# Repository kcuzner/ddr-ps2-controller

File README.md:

# Dance-Dance-Revolution PS2 Controller

Kevin Cuzner

## Introduction

This is my attempt at a low-cost, but high quality DIY DDR controller which is compatible with the Sony PlayStation 2.

The firmware is based loosely on my [Pop-N-Music PS2 Controller](https://github.com/kcuzner/pop-n-music-controller).
though I've rewritten it to be closer to my current style.

Although it would be cool to use an STM32 or other advanced ARM controller, that is overkill for what this is. Turns
out, a $0.60 AVR microcontroller can meet all the digital requirements without even needing a 3.3V regulator. To that
end, here is the main featureset:

 - ATTiny20 microcontroller (QFN package, 12 I/O). There are two personalities:
   - The PSX bus interface. This takes input from up to 6 buttons and operates the upstream PSX bus to the PlayStation
     2.
   - The switch controller. This takes input from up to 4 foot switches and produces a single output which is cabled to
     the PSX bux interface board.
 - Single PCB which fits both personalities.
 - Edge-facing LEDs for pad illumination.
   - Strangely enough, it was cheaper to just use a constant-current controlled LED driver than to use a discrete MOSFET
     of an appropriate size.

## Project Status

 - This project has not been fully assembled or tested. But:
 - Firmware builds and installs on both board personalities.
 - The LED/Switch boards work great! Mostly. Some quirks with the LEDs always being partially on,
   but whatever.
 - With a [USB-PS2 adapter](https://www.amazon.com/gp/product/B01J4JVFXI) I've verified on an
   oscilloscope that the controller board can be polled and that it appears to send back the
   correct responses. So the PSX bus implementation is at least superficially correct.
 - The switch boards can connect to the controller board and on an oscilloscope I've verified that
   everything toggles.

Some things still remain I can think of off the top of my head:

 - I need to test it with an actual PS2. Now to convince my wife to let me touch her PS2...
 - I need to verify that the button/switch mappings are correct for a dance pad. I unfortunately
   didn't mark the PCB silkscreen in any way for that, so I'm going to have to resort to colored
   tape, paint, or something else to keep the myriad cables straight while wiring this up.
 - I need to actually construct the wood/metal/plastic enclosure for this. I have a plan, but it's
   not posted here.

## References

 - http://www.raphnet.net/electronique/psx_adaptor/Playstation.txt
 - https://gist.github.com/scanlime/5042071
 - https://store.curiousinventor.com/guides/PS2/
 - https://blog.nearfuturelaboratory.com/2008/06/19/playstation2-logic-analysis/

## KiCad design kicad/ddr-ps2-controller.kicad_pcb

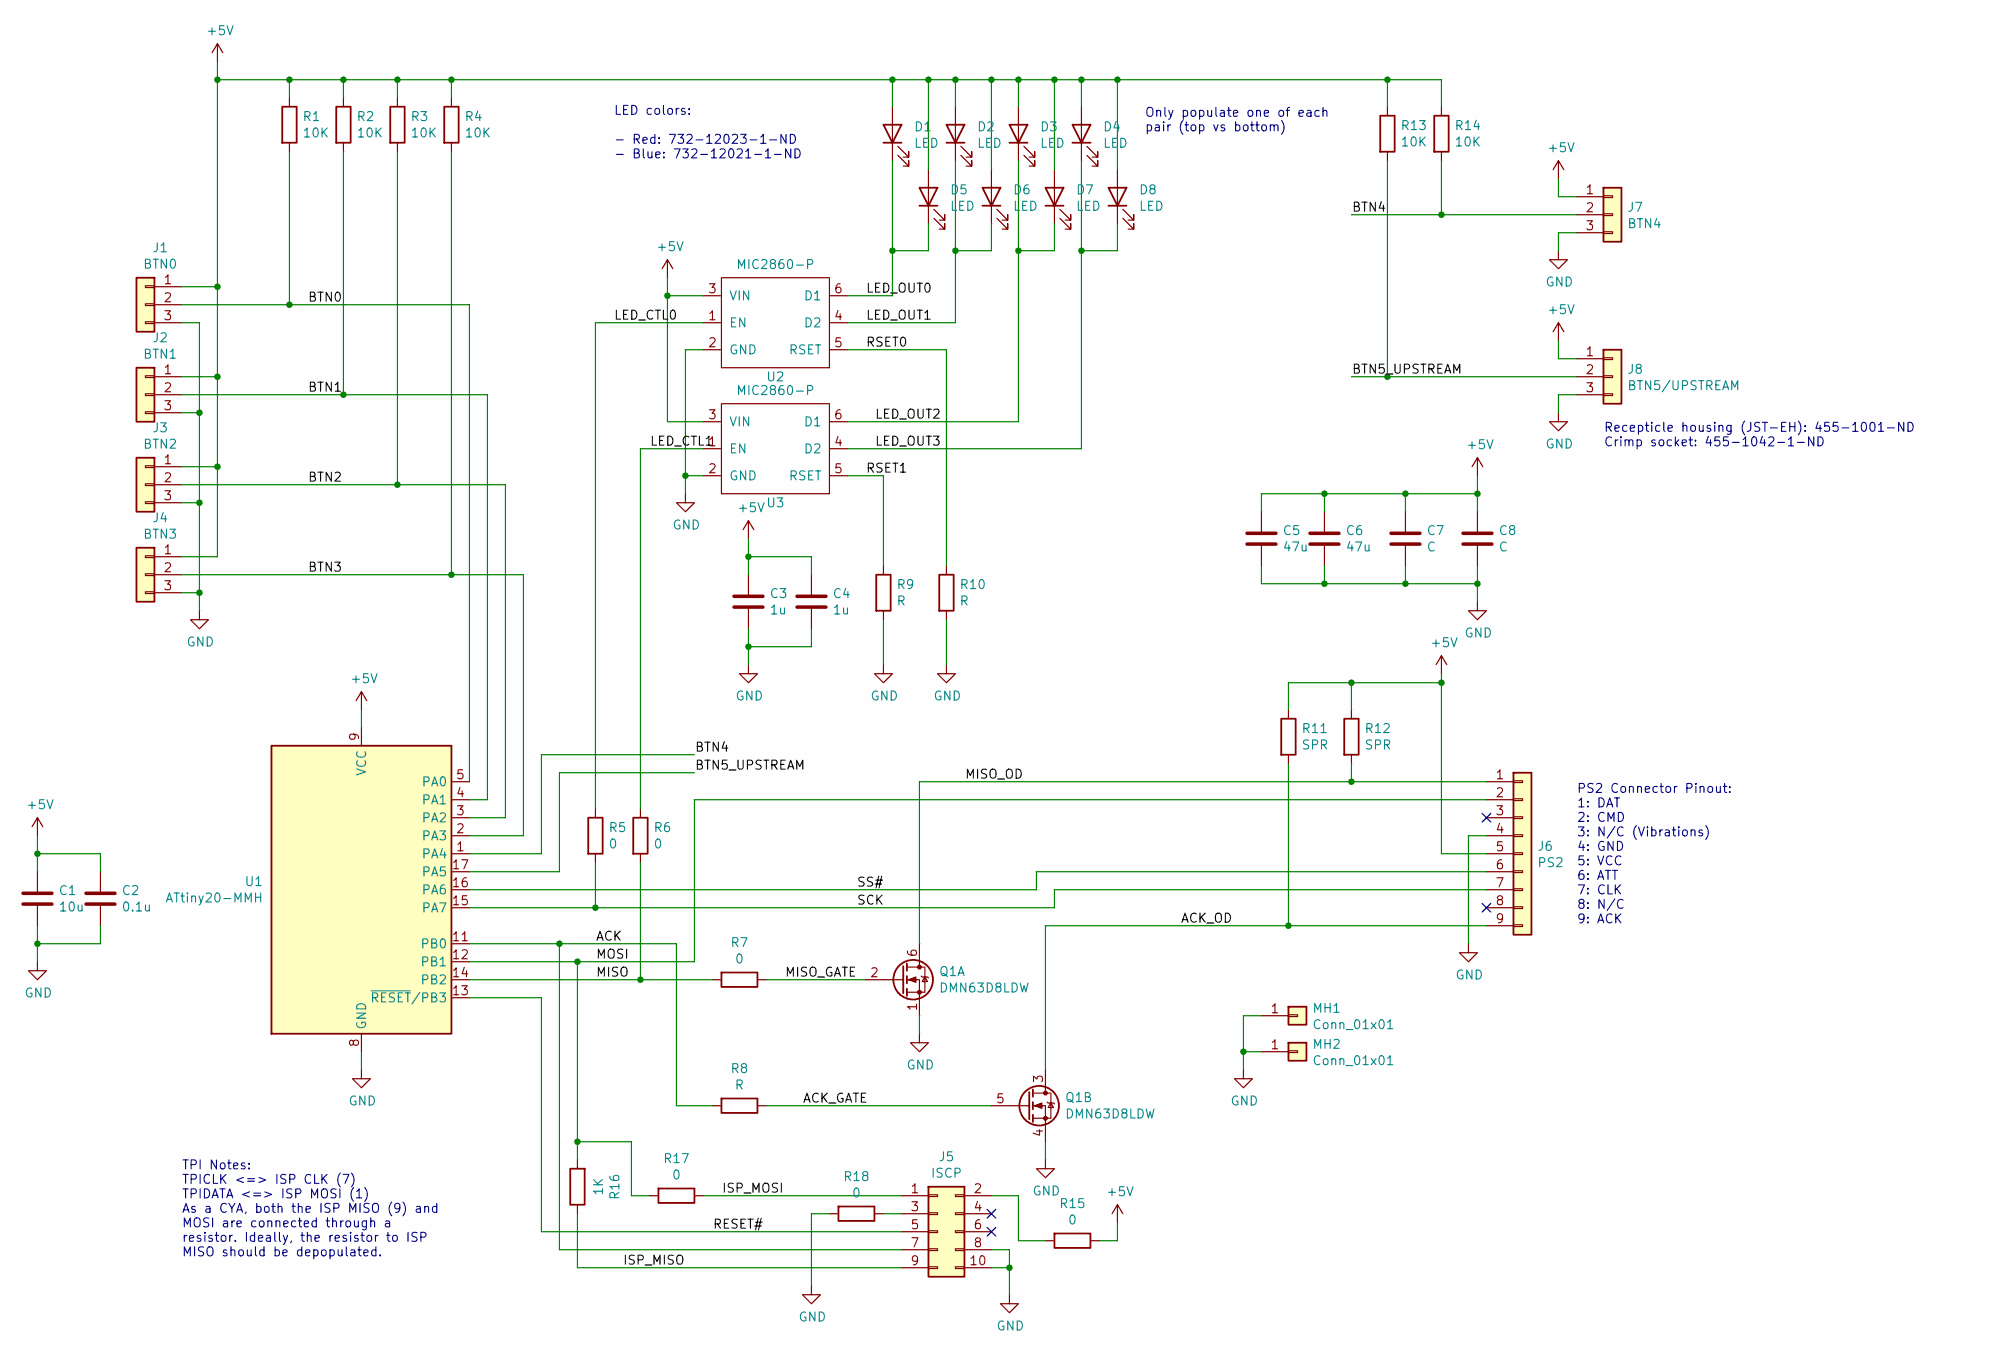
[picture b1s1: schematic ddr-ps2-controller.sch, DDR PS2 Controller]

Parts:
C1: 10u; C_0603_1608Metric
C2: 0.1u; R_0402_1005Metric
C3, C4: 1u; R_0402_1005Metric
C5, C6: 47u; C_1210_3225Metric; Part Number 587-1780-1-ND
C7, C8: C; C_0805_2012Metric
D1, D2, D3, D4, D5, D6, D7, D8: LED; Wurth_WL-SMSW_LED; Part Number 732-12021-1-ND
J1: BTN0; JST_EH_3_RA; Part Number 455-1626-ND
J2: BTN1; JST_EH_3_RA; Part Number 455-1626-ND
J3: BTN2; JST_EH_3_RA; Part Number 455-1626-ND
J4: BTN3; JST_EH_3_RA; Part Number 455-1626-ND
J5: ISCP; CnC_3020_10_0300
J6: PS2; PinHeader_1x09_P2.54mm_Vertical
J7: BTN4; JST_EH_3_RA; Part Number 455-1626-ND
J8: BTN5/UPSTREAM; JST_EH_3_RA; Part Number 455-1626-ND
MH1, MH2: Conn_01x01; MountingHole_4.3mm_M4_Pad_Via
Q1: DMN63D8LDW; SOT-363_SC-70-6; Part Number DMN63D8LDW-7CT-ND
R1, R2, R3, R4, R13, R14: 10K; R_0402_1005Metric
R5, R6, R7, R17: 0; R_0402_1005Metric
R8, R9, R10: R; R_0402_1005Metric
R11, R12: SPR; R_0402_1005Metric
R15, R18: 0; R_0603_1608Metric
R16: 1K; R_0402_1005Metric
U1: ATtiny20-MMH; QFN-20-1EP_3x3mm_P0.45mm_EP1.6x1.6mm; Part Number ATTINY20-MMH-ND
U2, U3: MIC2860-P; SOT-363_SC-70-6; Part Number 576-3897-1-ND

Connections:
+5V: C1.1, C2.1, C3.1, C4.1, C5.1, C6.1, C7.1, C8.1, D1.2 (A), D2.2 (A), D3.2 (A), D4.2 (A), D5.2 (A), D6.2 (A), D7.2 (A), D8.2 (A), J1.1, J2.1, J3.1, J4.1, J6.5, J7.1, J8.1, R1.1, R2.1, R3.1, R4.1, R11.1, R12.1, R13.1, R14.1, R15.1, U1.9 (VCC), U2.3 (VIN), U3.3 (VIN)
/ACK: J5.7, R8.2, U1.11 (PB0)
/ACK_GATE: Q1.5 (G), R8.1
/ACK_OD: J6.9, Q1.3 (D), R11.2
/BTN0: J1.2, R1.2, U1.5 (PA0)
/BTN1: J2.2, R2.2, U1.4 (PA1)
/BTN2: J3.2, R3.2, U1.3 (PA2)
/BTN3: J4.2, R4.2, U1.2 (PA3)
/BTN4: J7.2, R14.2, U1.1 (PA4)
/BTN5_UPSTREAM: J8.2, R13.2, U1.17 (PA5)
/ISP_MISO: J5.9, R16.1
/ISP_MOSI: J5.1, R17.1
/LED_CTL0: R5.1, U2.1 (EN)
/LED_CTL1: R6.1, U3.1 (EN)
/LED_OUT0: D1.1 (K), D5.1 (K), U2.6 (D1)
/LED_OUT1: D2.1 (K), D6.1 (K), U2.4 (D2)
/LED_OUT2: D3.1 (K), D7.1 (K), U3.6 (D1)
/LED_OUT3: D4.1 (K), D8.1 (K), U3.4 (D2)
/MISO: R6.2, R7.2, U1.14 (PB2)
/MISO_GATE: Q1.2 (G), R7.1
/MISO_OD: J6.1, Q1.6 (D), R12.2
/MOSI: J6.2, R16.2, R17.2, U1.12 (PB1)
/RESET#: J5.5, U1.13 (~RESET~/PB3)
/RSET0: R10.1, U2.5 (RSET)
/RSET1: R9.1, U3.5 (RSET)
/SCK: J6.7, R5.2, U1.15 (PA7)
/SS#: J6.6, U1.16 (PA6)
GND: C1.2, C2.2, C3.2, C4.2, C5.2, C6.2, C7.2, C8.2, J1.3, J2.3, J3.3, J4.3, J5.8, J5.10, J6.4, J7.3, J8.3, MH1.1, MH2.1, Q1.1 (S), Q1.4 (S), R9.2, R10.2, R18.2, U1.8 (GND), U1.21 (GND), U2.2 (GND), U3.2 (GND)
unnamed: J5.2, R15.2
unnamed: J5.3, R18.1

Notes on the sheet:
LED colors: - Red: 732-12023-1-ND - Blue: 732-12021-1-ND
PS2 Connector Pinout: 1: DAT 2: CMD 3: N/C (Vibrations) 4: GND 5: VCC 6: ATT 7: CLK 8: N/C 9: ACK
Recepticle housing (JST-EH): 455-1001-ND‎ Crimp socket: 455-1042-1-ND‎
Only populate one of each pair (top vs bottom)
TPI Notes: TPICLK <=> ISP CLK (7) TPIDATA <=> ISP MOSI (1) As a CYA, both the ISP MISO (9) and MOSI are connected through a resistor. Ideally, the resistor to ISP MISO should be depopulated.

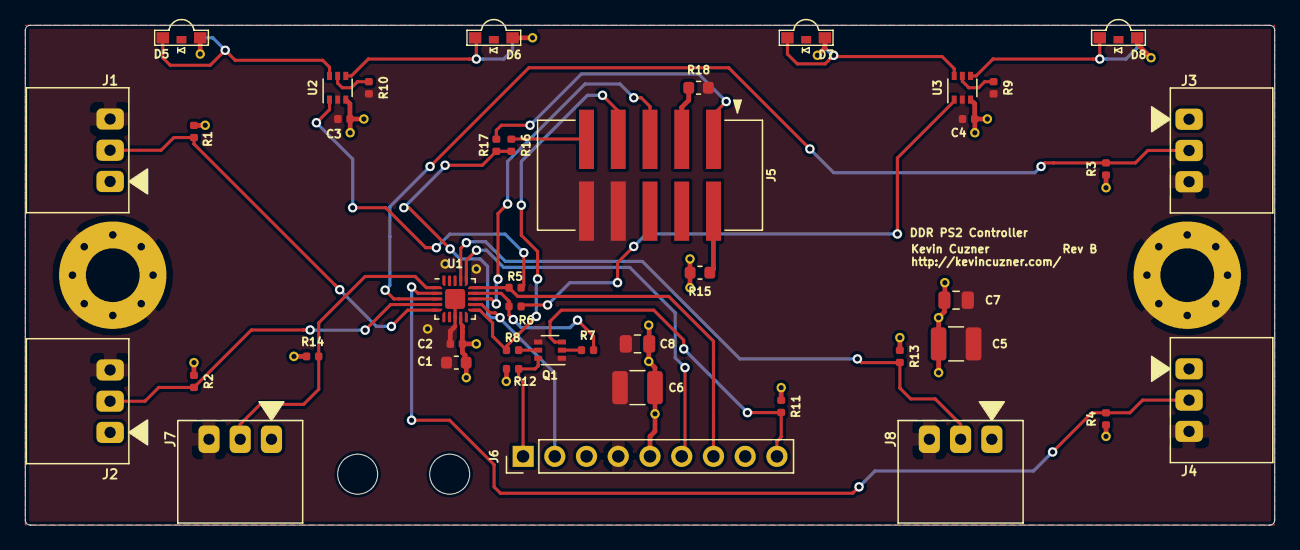
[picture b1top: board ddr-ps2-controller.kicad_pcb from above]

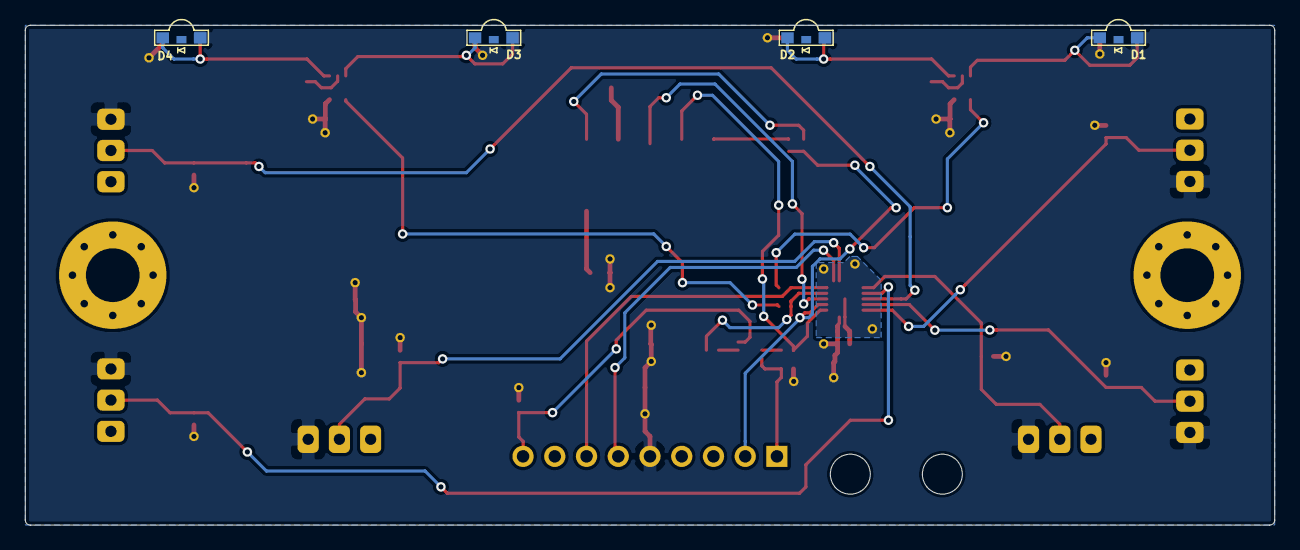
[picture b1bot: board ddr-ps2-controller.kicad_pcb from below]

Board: 2 copper layers, 100.0 x 40.0 mm, 48 parts (4 on the bottom side), 30 nets.

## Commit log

2019-06-13 Initial PCB layout with CAD files for new footprints
2019-06-13 Adding firmware build structure
2019-06-13 Improved top-level makefile and added some documentation
2019-06-16 Added "fuse" support
    Strictly speaking, it is not fuses. It is a particular region of
    configuration memory. But it is called a fuse in the datasheet and it is
    a shame that it isn't supported by the AVR stdlib.
2019-06-18 Added common source and include for pins
2019-08-08 Changed connector to the far cheaper JST-EH
2019-08-08 Added rounding to the board edges
2019-08-08 Minor cleanup with LED alignment
2019-08-08 Fixing board outline shape issue
2019-08-17 Rev A Gerber out
2019-08-18 Adding initial PSX bus implementation and scaffold for pad impl
    My previous design had a bunch of stuff in main. While this is fine, I
    want this to be just a bit more modular. So I'm separating the PSX bus
    layer from the controller and making the controller implementation a
    module of its own.
2019-08-19 Added initial pad implementation
    This is not very efficient, as it reads the port each time it asks for
    the pin state. I may end up going back to how I did it with the
    popnmusic controller, although that wasn't very fancy.
2019-08-20 Added LED system for the switch component
2019-09-21 Removed a random unprintable charcter from some part numbers
2019-09-21 Reduced stencil size to fit on printer
2019-09-21 First pass at the solder stencil
2019-09-21 Added datasheet for micrel LED driver
2019-10-07 Many small changes to get the switch firmware working
    It now works, though I suspect my first board is defective on at least
    one switch (just need to run the iron over the pins again on one side
    that's a little light).
2020-10-25 Updating PCB and Schematic for rev B, fixing TPI and footprint issues
    The programming interface for this microcontroller is TPI and for some
    reason I wired it to be ISP. This implements a greenwire I did to work
    around it.
    I did not double-check the footprint for the SMD header. I've now added
    the footprint from the datasheet.
    Schematic library updated
2022-09-10 Decreasing latency for servicing PSX ISR, getting valid data
2022-09-11 Adding idle data byte to PSX
2022-09-11 Fixing MISO bad-actor behavior after SS# deassert
2022-09-11 Fixing button press polarity
2022-09-11 Updating project status
2022-09-11 Adding references so I don't forget later
